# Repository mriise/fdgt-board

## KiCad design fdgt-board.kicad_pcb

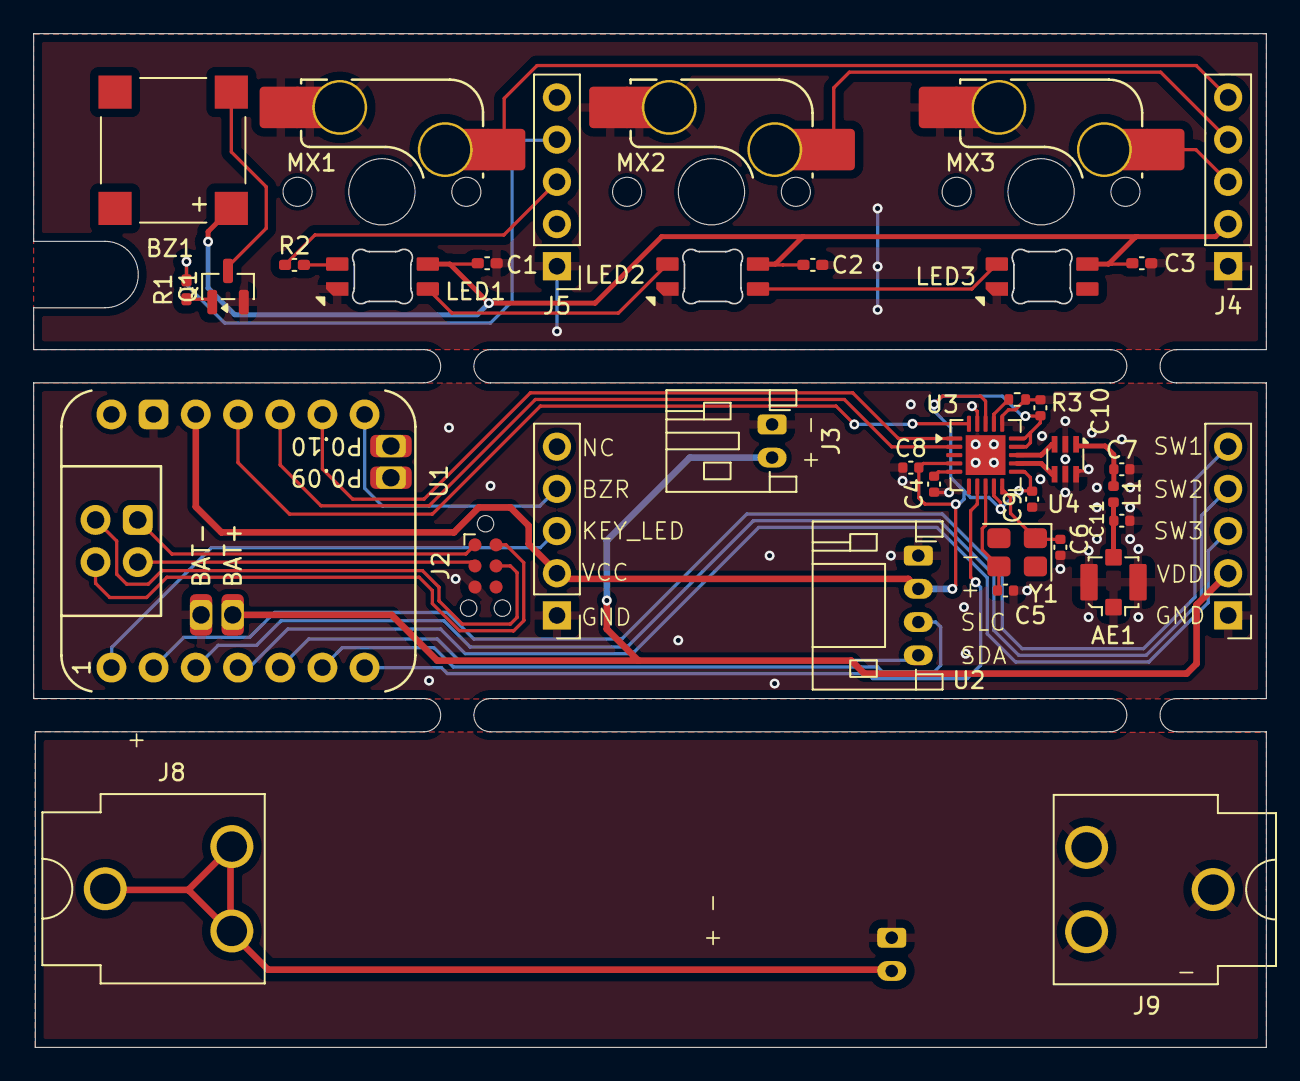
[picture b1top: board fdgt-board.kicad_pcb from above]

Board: 2 copper layers, 74.2 x 61.0 mm, 38 parts (1 on the bottom side), 31 nets.

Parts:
AE1: Antenna; U.FL_Molex_MCRF_73412-0110_Vertical
BZ1: Buzzer; PUIAudio_SMT_0825_S_4_R
C1, C2, C3: 100nF; C_0402_1005Metric_Pad0.74x0.62mm_HandSolder
C4, C8, C9, C10: 100nF; C_0402_1005Metric
C5, C6: 15pF; C_0402_1005Metric
C7, C11: 5.6pF; C_0402_1005Metric
J1, J3: BAT; JST_PH_S2B-PH-K_1x02_P2.00mm_Horizontal
J2: Conn_ARM_SWD_TagConnect_TC2030-NL; Tag-Connect_TC2030-IDC-NL_2x03_P1.27mm_Vertical
J4, J5, J6, J7: Conn_01x05; PinHeader_1x05_P2.54mm_Vertical
J8, J9: Keystone 54; BatteryClip_Keystone_54_D16-19mm
L1: 27nH; L_0402_1005Metric
LED1, LED2, LED3: MX_LED_6028R; LED_MX_6028R
MX1, MX2, MX3: MX_SW_HS; SW_MX_HS_CPG151101S11_1u
Q1: MMBT2222A; SOT-23
R1: 1k; C_0402_1005Metric_Pad0.74x0.62mm_HandSolder
R2: 220R; C_0402_1005Metric_Pad0.74x0.62mm_HandSolder
R3: 56k; R_0402_1005Metric
U1: Seeeduino Xiao nRF52840; Xiao_nRF52840_ACH
U2: SSD1306; JST_PH_S4B-PH-K_1x04_P2.00mm_Horizontal
U3: CC1101; Texas_RGP0020H_VQFN-20-1EP_4x4mm_P0.5mm_EP2.4x2.4mm
U4: HHM1591D1; Balun_Johanson_0896BM15A0001
Y1: 26MHz; Crystal_SMD_3225-4Pin_3.2x2.5mm

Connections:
/AE: AE1.1 (A), C11.1, L1.2
/RF_N: U3.13 (RF_N), U4.3
/RF_P: U3.12 (RF_P), U4.4
BZR: J5.4, J6.4, R1.1, U1.14 (P1.12)
CLK: U1.13 (P1.13), U3.1 (SCLK)
CS_Radio: U1.7 (P1.11), U3.7 (CS)
DSPLY_SDA: U1.5 (P0.04), U2.4
DSPLY_SLC: U1.6 (P0.05), U2.3
KEY_LED: J5.3, J6.3, R2.1, U1.1 (P0.02)
MISO: U1.12 (P1.14), U3.2 (SO/GDO1)
MOSI: U1.11 (P1.15), U3.20 (SI)
unnamed: BZ1.2 (-), Q1.3 (C)
unnamed: C7.1, L1.1, U4.1
unnamed: J2.4 (SWCLK), U1.20 (CLK)
unnamed: J2.2 (SWDIO), U1.19 (DIO)
unnamed: J2.1 (VCC), U1.22 (GND)
unnamed: J2.3 (~RESET), U1.21 (RST)
unnamed: LED1.3 (DIN), R2.2
unnamed: LED1.2 (DOUT), LED2.3 (DIN)
unnamed: LED2.2 (DOUT), LED3.3 (DIN)
unnamed: Q1.1 (B), R1.2
unnamed: C4.1, U3.5 (DCOUPL)
unnamed: R3.2, U3.17 (RBIAS)
unnamed: C5.1, U3.8 (XOSC_Q1), Y1.3
unnamed: C6.1, U3.10 (XOSC_Q2), Y1.1
SW1: J4.5, J7.5, MX1.1, U1.2 (P0.03)
SW2: J4.4, J7.4, MX2.1, U1.3 (P0.28)
SW3: J4.3, J7.3, MX3.1, U1.4 (P0.29)
VCC: C8.2, C9.2, C10.2, J5.2, J6.2, U1.10 (3V3), U2.2, U3.4 (DVDD), U3.9 (AVDD1), U3.11 (AVDD2), U3.14 (AVDD3), U3.15 (AVDD4), U3.18 (DGUARD)
VDD: BZ1.1 (+), C1.2, C2.2, C3.2, J1.2, J3.2, J4.2, J7.2, J8.1, LED1.1 (VDD), LED2.1 (VDD), LED3.1 (VDD), U1.16 (BAT+)
VSS: AE1.2 (Shield), C1.1, C2.1, C3.1, C4.2, C5.2, C6.2, C7.2, C8.1, C9.1, C10.1, C11.2, J1.1, J2.5 (GND), J3.1, J4.1, J5.1, J6.1, J7.1, J9.1, LED1.4 (VSS), LED2.4 (VSS), LED3.4 (VSS), MX1.2, MX2.2, MX3.2, Q1.2 (E), R3.1, U1.9 (GND), U1.15 (BAT-), U2.1, U3.16 (GND1), U3.19 (GND2), U3.21 (PAD), U4.2 (GND), U4.5 (GND), U4.6 (GND)

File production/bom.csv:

Designator,Footprint,Quantity,Value,LCSC Part #
AE1,U.FL_Molex_MCRF_73412-0110_Vertical,1,Antenna,
BZ1,PUIAudio_SMT_0825_S_4_R,1,Buzzer,
"C1, C10, C2, C3, C4, C8, C9",0402,7,100nF,
"C11, C7",0402,2,5.6pF,
"C5, C6",0402,2,15pF,
"J8, J9",BatteryClip_Keystone_54_D16-19mm,2,Keystone 54,
L1,0402,1,27nH,
"LED1, LED2, LED3",LED_MX_6028R,3,MX_LED_6028R,
"MOUSE-BITE-2MM-SLOT_4, MOUSE-BITE-2MM-SLOT_3, MOUSE-BITE-2MM-SLOT_2, MOUSE-BITE-2MM-SLOT",mouse-bite-2mm-slot,4,VAL**,
"MX1, MX2, MX3",SW_MX_HS_CPG151101S11_1u,3,MX_SW_HS,
Q1,SOT-23,1,MMBT2222A,
R1,0402,1,1k R,
R2,0402,1,220R,
R3,0402,1,56k,
U3,Texas_RGP0020H_VQFN-20-1EP_4x4mm_P0.5mm_EP2.4x2.4mm,1,CC1101,
U4,Balun_Johanson_0896BM15A0001,1,HHM1591D1,
Y1,Crystal_SMD_3225-4Pin_3.2x2.5mm,1,26MHz,

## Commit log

2026-04-10 feat: sakura con changes & fixes (i can read mosi/miso just fine)
2026-04-10 fix: dont commit with project open
